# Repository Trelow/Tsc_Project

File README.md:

# OpenBook Reader

```mermaid
graph TD
    
    USB["USB-C Connector(ESD Protection)"] -->|5V| CHG["Battery Charger (MCP73831)"]
    CHG -->|Charging| BATT["Li-Po Battery (2500mAh)"]
    BATT --> LDO["3.3V LDO Regulator (XC6220)"]

    LDO -->|3.3V| ESP["ESP32-C6-WROOM-1(MCU)"]

    ESP -- I2C --> RTC["Real Time Clock(DS3231)"]
    ESP -- I2C --> BME["Environmental Sensor(BME688)"]
    ESP -- I2C --> FUEL["Battery Fuel Gauge(MAX17048)"]
    ESP -- I2C --> QWIIC["Qwiic / Stemma QT"]

    ESP -- SPI --> FLASH["External NOR Flash(W25Q512)"]
    ESP -- SPI --> SD["MicroSD Card Slot"]
    ESP -- SPI --> EPD_HEADER["E-Paper Display Header"]

    EPD_HEADER --> EPD_DRIVER["EPD Driver Circuit"]
    EPD_DRIVER --> EPD_POW["EPD HV Power"]
    LDO --> EPD_HEADER

    ESP -- GPIO --> BUTTONS["3x Buttons:BOOT, CHANGE, RESET"]

    USB -- USB D+/D- --> ESP
```

## Tabel Componente Principale (BOM)

| Parts | Device | Check Prices | Datasheet |
|-------|--------|--------------|-----------|
|R1, R2 .. | ESP32_WROVER_EAGLE-LTSPICE_RR0402 |https://componentsearchengine.com/part-view/R0402%201%25%20100%20K%20                   | https://componentsearchengine.com/part-view/R0402%201%25%20100%20K%20      |
| L1 | 744043680IND_4828-WE-TPC_WRE |  https://eu.mouser.com/ProductDetail/Wurth-Elektronik/744043680?qs=PGXP4M47uW6VkZq%252BkzjrHA%3D%3D               | https://eu.mouser.com/ProductDetail/Wurth-Elektronik/744043680?qs=PGXP4M47uW6VkZq%252BkzjrHA%3D%3D               |
| IC1 | BD5229G-TR |https://componentsearchengine.com/part-view/BD5229G-TR/ROHM%20Semiconductor                                    | https://componentsearchengine.com/part-view/BD5229G-TR/ROHM%20Semiconductor                                    |
| SENSOR2 | ESP32_WROVER_BME680_BME680 | https://www.snapeda.com/parts/BME680/Bosch/view-part/?welcome=home                                            | https://www.snapeda.com/parts/BME680/Bosch/view-part/?welcome=home                                            |
| SJ1              | SJ                                           | https://grabcad.com/library/solder-jumpers-1                                                                   | https://grabcad.com/library/solder-jumpers-1                                                                   |
| BOOT_BUTTON, CHANGE_BUTTON, RESET_BUTTON | BUTTON_CUSYOMV1 | https://industry.panasonic.com/global/en/products/control/switch/light-touch/number/evqpuj02k                  | https://industry.panasonic.com/global/en/products/control/switch/light-touch/number/evqpuj02k                  |
| C1, C2 .. | CPH3225A | https://www.snapeda.com/parts/CPH3225A/Seiko+Instruments/view-part/?ref=eda | - |
| U3 | DS3231SN# | https://www.snapeda.com/parts/DS3231SN%23/Analog+Devices/view-part/?ref=eda | [Datasheet](https://www.analog.com/media/en/technical-documentation/data-sheets/ds3231.pdf) |
| U2 | ESP32-C6-WROOM-1-N8 | https://www.snapeda.com/parts/ESP32-C6-WROOM-1-N8/Espressif+Systems/view-part/?ref=eda | - |
| PFMF.050.1 | ESP32C6_VARISTORCN1812| https://www.mouser.co.uk/ProductDetail/EPCOS-TDK/B72520T0350K062?qs=dEfas%2FXlABIszF52uu7vrg%3D%3D              | https://www.mouser.co.uk/ProductDetail/EPCOS-TDK/B72520T0350K062?qs=dEfas%2FXlABIszF52uu7vrg%3D%3D              |
| D2 | ESP32_WROVER_AVX---SD0805S020S1R0 | https://eu.mouser.com/ProductDetail/KYOCERA-AVX/SD0805S020S1R0?qs=jCA%252BPfw4LHbpkAoSnwrdjw%3D%3D              | http://datasheets.avx.com/schottky.pdf                                                                         |
| MCP73831 | ESP32_WROVER_SPARKFUN-IC-POWER_MCP73831 |  https://eu.mouser.com/ProductDetail/Microchip-Technology/MCP73831T-2ACI-OT?qs=yUQqVecv4qvbBQBGbHx0Mw%3D%3Dcf   |
| J1 | FH34SRJ-24S-0.5SH_99_ | https://componentsearchengine.com/part-view/XC6220A331MR-G/Torex                                              | https://componentsearchengine.com/part-view/XC6220A331MR-G/Torex                                              |
| U4 | MAX17048G+T10 | https://www.snapeda.com/parts/MAX17048G+T10/Analog+Devices/view-part/?ref=eda | - |
| D3, D4, D5 | MBR0530 | https://www.snapeda.com/parts/MBR0530/Onsemi/view-part/?ref=eda | - |
| D6, D8, D9, D10, D11, D12 | PGB1010603MR | https://www.snapeda.com/parts/PGB1010603MR/Littelfuse/view-part/?ref=eda | - |
| J3 | QWIIC_CONNECTORJS-1MM | - | - |
| J2 | SAMACSYS_PARTS_USB4110-GF-A |https://www.mouser.com/ProductDetail/GCT/USB4110-GF-A | https://gct.co/files/drawings/usb4110.pdf |
| D7 | ESP32_WROVER_AVX---SD0805S020S1R0 | - | [Datasheet](http://datasheets.avx.com/schottky.pdf) |
| BOOT_BUTTON | EVQPUJ02K | https://www.mouser.com/ProductDetail/Panasonic/EVQPUJ02K | [Datasheet](https://na.industrial.panasonic.com/file-download/21900) |
| Q3 | SI1308EDL-T1-GE3 | https://componentsearchengine.com/part-view/SI1308EDL-T1-GE3/Vishay                                           | https://componentsearchengine.com/part-view/SI1308EDL-T1-GE3/Vishay                                           |
| TP1, TP2, ..., TP17 | TPTP20R | - | - |
| D1 | USBLC6-2SC6Y |  https://www.snapeda.com/parts/USBLC6-2SC6Y/STMicroelectronics/view-part/?ref=eda                              | https://www.snapeda.com/parts/USBLC6-2SC6Y/STMicroelectronics/view-part/?ref=eda                              |
| U1 | W25Q512JVEIQ | https://www.snapeda.com/parts/W25Q512JVEIQ/Winbond+Electronics/view-part/?ref=eda | - |
| IC4 | XC6220A331MR-G | https://www.mouser.com/ProductDetail/Torex-Semiconductor/XC6220A331MR-G) | https://www.torexsemi.com/file/xc6220/XC6220.pdf |

## Descriere Detaliată a Funcționalității Hardware

### 1. Microcontroller – ESP32-C6
Dispozitivul folosește microcontroller-ul ESP32-C6-WROOM-1-N8, echipat cu un nucleu RISC-V pe 32 de biți, cu o frecvență maximă de 160 MHz.

- **Memorie:** 512 KB SRAM internă și flash extern de 8 MB (W25Q512JVEIQ).
- **Conectivitate:** Wi-Fi 6, Bluetooth 5 LE, interfață USB 2.0.
- **Periferice:** Suport SPI, I²C, UART și GPIO multipli.
- **Eficiență energetică:** Moduri sleep și deep sleep optimizate pentru utilizarea eficientă a bateriei.

### 2. Afișaj E-Paper
Afișaj E-Ink de 7.5” cu rezoluție de 800×480 pixeli

- **Interfață:** SPI 4-wire cu pini adiționali (CS, DC, RST, BUSY).
- **Consum:** Foarte redus în stare statică; crește doar temporar în timpul actualizării imaginii (aproximativ 15-25 mA).
- **Beneficii:** Imaginea este păstrată fără consum electric, ideal pentru dispozitive portabile tip e-reader.

### 3. Senzor Mediu – BME680
Senzor multifuncțional care măsoară temperatura, umiditatea, presiunea atmosferică și calitatea aerului (VOC/eCO₂).

- **Interfață:** I²C cu viteză de până la 400 kHz.
- **Consum:** Aproximativ 2.1µA în mod standby și câțiva mA la citiri active.
- **Avantaj principal:** Integrează multiple funcții de mediu într-un singur cip compact și eficient.

### 4. Management Energetic & Baterie
Sistemul energetic este bazat pe o baterie Li-Po de 3.7V și capacitate de 2500mAh, pentru autonomie extinsă.

- **Încărcare:** MCP73831, încărcare rapidă prin USB-C (maxim 1A).
- **Monitorizare:** MAX17048 comunică starea bateriei prin interfața I²C.
- **Regulator:** XC6220A331MR-G oferă tensiunea stabilă de 3.3V pentru componentele critice.

### 5. Interfață Utilizator – Butoane
Sunt incluse trei butoane tactile dedicate navigării, selecției și întoarcerii paginilor, fiecare conectat la GPIO cu debouncing hardware (rezistor și condensator) sau software.

### 6. Conector USB-C
- **Funcții principale:** Încărcarea acumulatorului, transferul de date (USB 2.0) și actualizarea firmware-ului. Utilizare de diode ESD (ex: USBLC6-2SC6Y) și rezistențe specifice pentru conformitate cu USB-C.

### 8. Slot MicroSD (112A-TAAR-R03)
- **Utilizare:** Stocare log-uri, cărți electronice și actualizări de firmware.
- **Interfață:** Compatibil cu SD (mod 1-bit sau 4-bit) sau SPI, configurabil în firmware.

### 8. Conector Qwiic (I²C)
Conector standardizat cu patru pini (VCC, GND, SDA, SCL) pentru extinderea rapidă a funcționalităților prin senzori sau module suplimentare.

### 9. RTC DS3231
- **Precizie:** Foarte ridicată.
- **Interfață:** Comunicare I²C integrată cu ceilalți senzori.

### 10. Memorie Flash Externă – W25Q512JVEIQ
- **Interfață:** Quad SPI pentru acces rapid la date.
- **Utilizare:** Stocarea aplicațiilor, imaginilor și fișierelor mari, inclusiv cărți electronice.

## Estimare Consum Energetic
- **Activ (Wi-Fi + refresh ecran):** Aproximativ 150 mA
- **Citire (ecran static):** Aproximativ 10 mA
- **Deep Sleep:** Sub 50 µA
- **Autonomie:** Aproximativ o săptămână, considerând un consum mediu de 10 mA (2500mAh ~250 ore utilizare).

## Estimare Consum de Energie
- **Activ (Wi-Fi + Refresh ecran)**: ~150mA  
- **Citire (ecran static)**: ~10mA  
- **Deep Sleep**: <50µA  
- **Autonomie estimată**: ~1 săptămână (la o utilizare medie de 10mA, o baterie de 2500mAh durează ~250 ore).

---

## Atribuirea Pinilor pe ESP32-C6

| Pin  | Funcție        | Componentă          | Descriere Utilizare           |
|-----:|:---------------|:--------------------|:------------------------------|
| GPIO0  | BOOT_BUTTON    | Buton               | Boot mode la pornire          |
| GPIO1  | RESET_BUTTON   | Buton               | Reset manual                  |
| GPIO2  | CHANGE_BUTTON  | Buton               | Navigare meniu                |
| GPIO3  | EPD_CS         | Display E-Paper     | Chip Select (SPI)             |
| GPIO4  | EPD_DC         | Display E-Paper     | Data/Command control          |
| GPIO5  | EPD_RST        | Display E-Paper     | Reset ecran                   |
| GPIO6  | EPD_BUSY       | Display E-Paper     | Semnal stare refresh          |
| GPIO7  | SPI_MOSI       | Display, Flash, SD  | Master Out Slave In (SPI)     |
| GPIO8  | SPI_MISO       | Display, Flash, SD  | Master In Slave Out (SPI)     |
| GPIO9  | SPI_SCK        | Display, Flash, SD  | Clock SPI                     |
| GPIO10 | FLASH_CS       | W25Q512JVEIQ        | Chip Select pentru Flash      |
| GPIO11 | SD_CS          | Micro SD (opțional) | Chip Select card SD           |
| GPIO12 | I2C_SDA        | BME680, MAX17048, DS3231 | Linie date I2C          |
| GPIO13 | I2C_SCL        | BME680, MAX17048, DS3231 | Linie clock I2C         |
| GPIO14 | CHG_LED        | LED încărcare       | Status încărcare              |
| GPIO15 | UART_TX        | Debugging           | TX serial                     |
| GPIO16 | UART_RX        | Debugging           | RX serial                     |
| GPIO17 | USB_D+         | USB-C               | Linie date USB +              |
| GPIO18 | USB_D-         | USB-C               | Linie date USB –              |

---

## Concluzii
Prin acest README, aveți la dispoziție elementele cheie ale construcției hardware pentru e-reader-ul **OpenBook**: modulul ESP32-C6, ecranul e-paper, senzorii, alimentarea și circuitele de încărcare. Fișierul CSV atașat oferă o listă detaliată a componentelor (BOM).

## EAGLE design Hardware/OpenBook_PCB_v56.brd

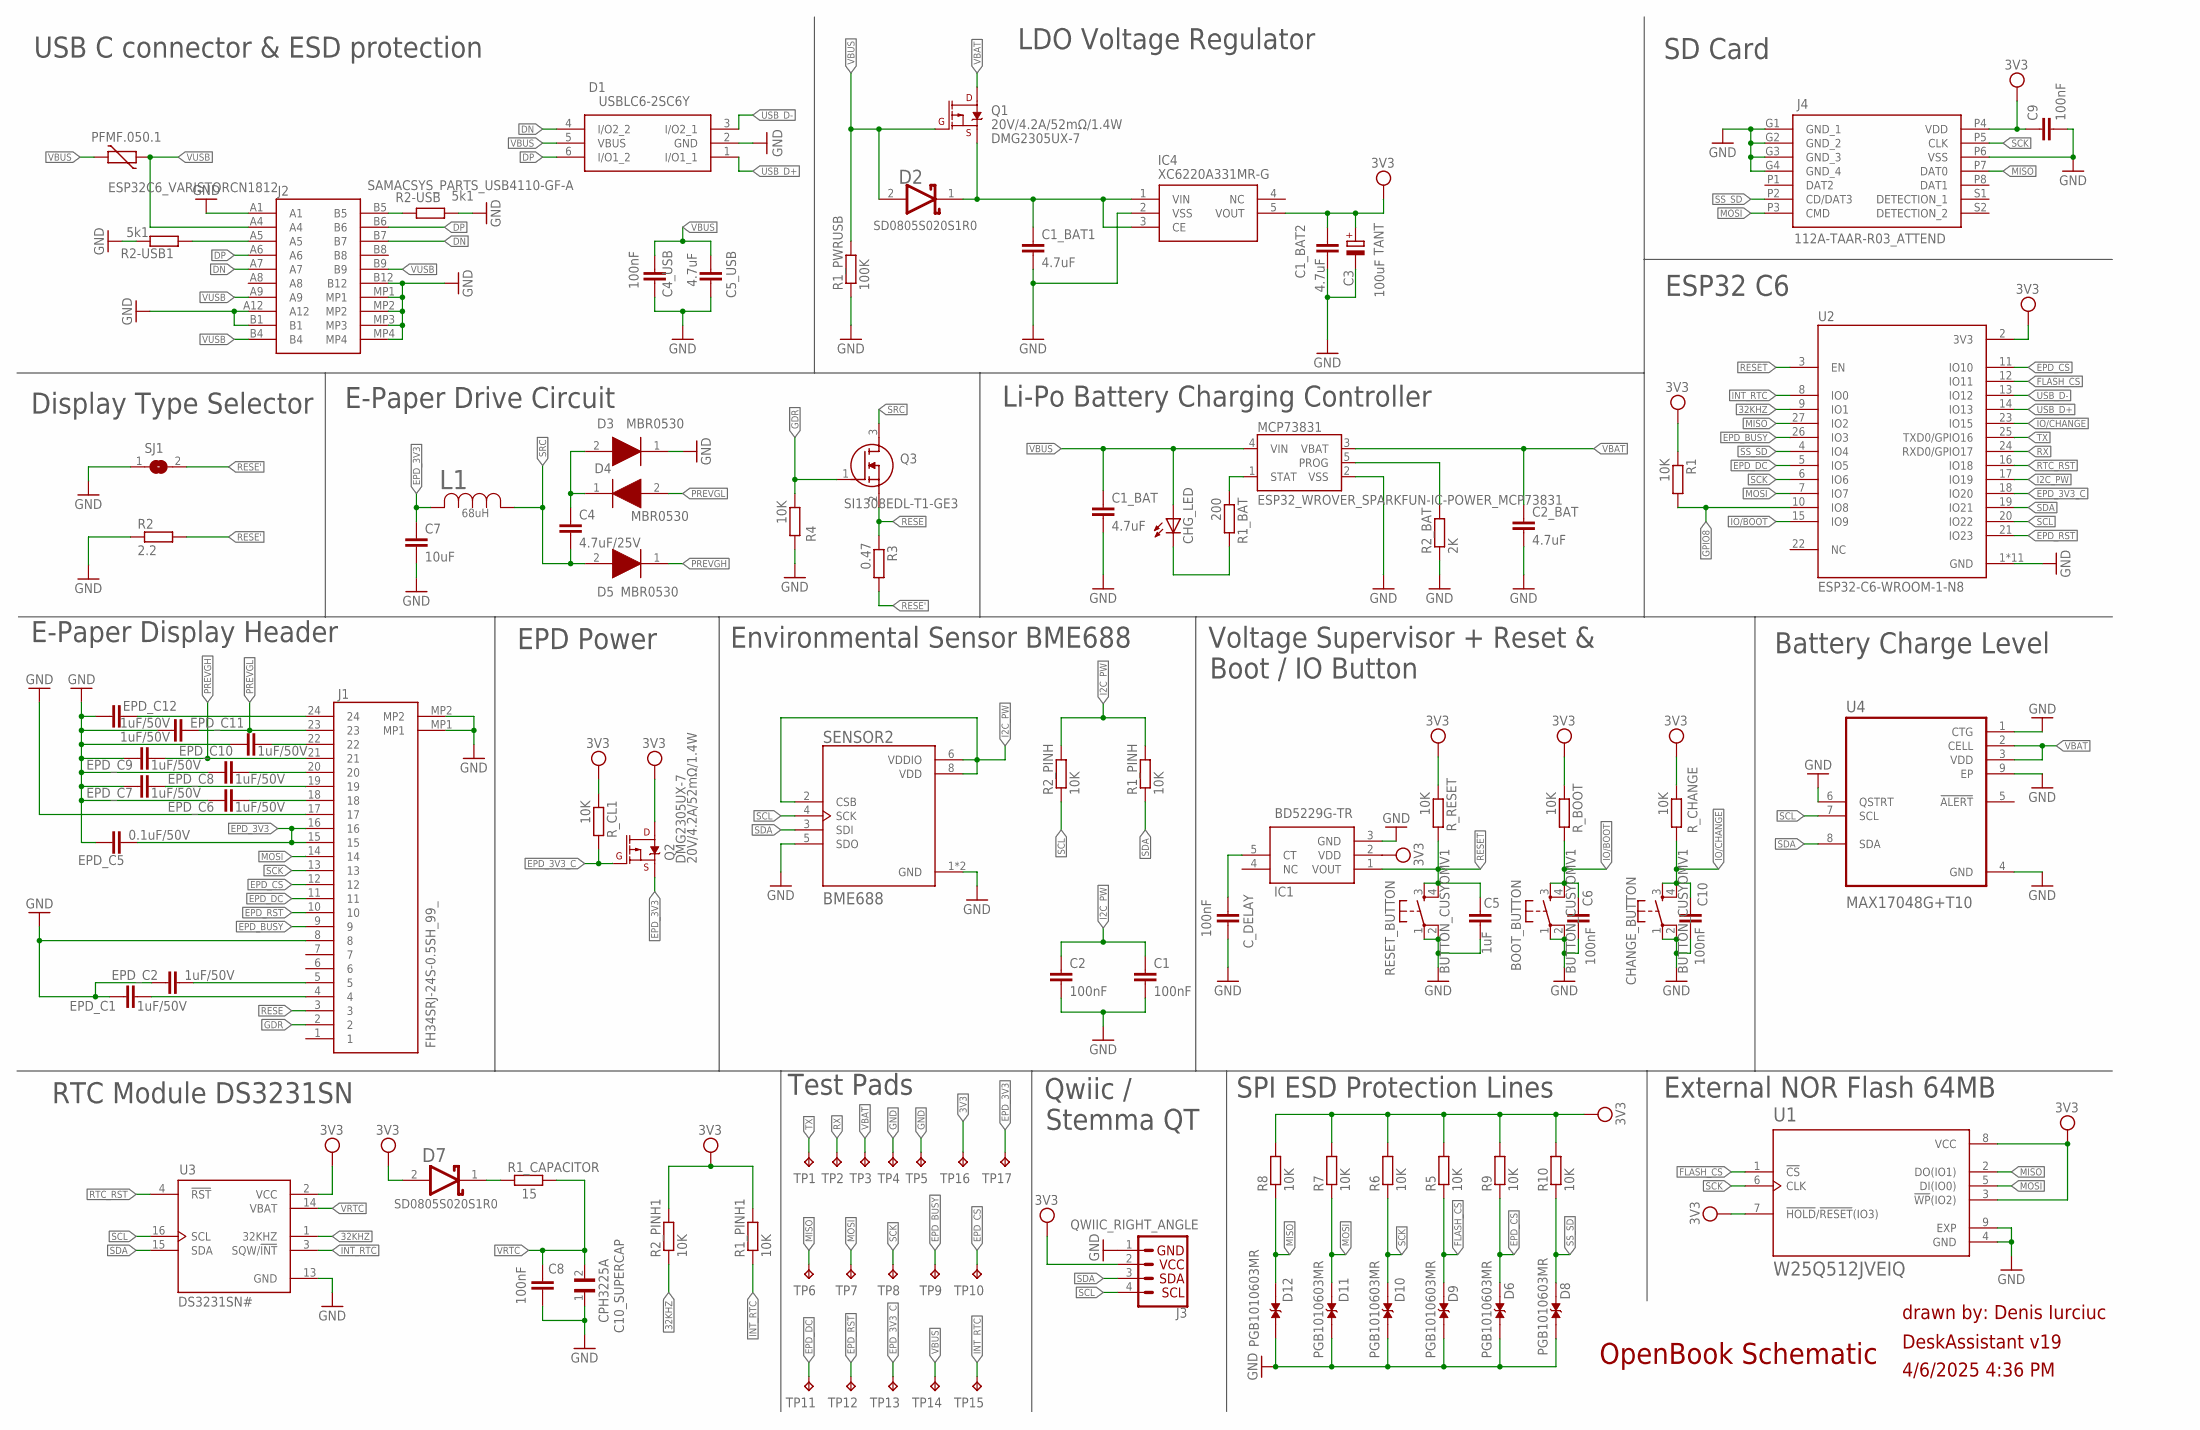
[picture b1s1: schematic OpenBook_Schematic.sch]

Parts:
BOOT_BUTTON: BUTTON_CUSYOMV1; MYBUTTON
C1, C2, C4_USB, C6, C8, C9, C10: 100nF; ESP32_WROVER_EAGLE-LTSPICE_C0402
C1_BAT, C1_BAT1, C1_BAT2, C2_BAT, C5_USB: 4.7uF; ESP32_WROVER_EAGLE-LTSPICE_C0402
C3: 100uF; RCL_CT3528
C4: 4.7uF/25V; ESP32_WROVER_EAGLE-LTSPICE_C0402
C5: 1uF; ESP32_WROVER_EAGLE-LTSPICE_C0402
C7: 10uF; ESP32_WROVER_EAGLE-LTSPICE_C0402
C10_SUPERCAP: CPH3225A; CAPCP3225X100N
CHANGE_BUTTON: BUTTON_CUSYOMV1; MYBUTTON
CHG_LED: ADAFRUIT_LEDCHIP-LED0603; ADAFRUIT_CHIP-LED0603
C_DELAY: 100nF; ESP32_WROVER_EAGLE-LTSPICE_C0402
D1: USBLC6-2SC6Y; SOT95P280X145-6N
D2: ESP32_WROVER_AVX---SD0805S020S1R0_AVX_SD0805S020S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; ESP32_WROVER_AVX---SD0805S020S1R0_AVX_SD0805S020S1R0_0
D3, D4, D5: MBR0530; SOD3716X135N
D6, D8, D9, D10, D11, D12: PGB1010603MR; DIOC1608X36N
D7: SD0805S020S1R0; ESP32_WROVER_AVX---SD0805S020S1R0_AVX_SD0805S020S1R0_0
EPD_C1, EPD_C2, EPD_C6, EPD_C7, EPD_C8, EPD_C9, EPD_C10, EPD_C11, EPD_C12: 1uF/50V; ESP32_WROVER_EAGLE-LTSPICE_C0402
EPD_C5: 0.1uF/50V; ESP32_WROVER_EAGLE-LTSPICE_C0402
IC1: BD5229G-TR; SOT95P280X125-5N
IC4: XC6220A331MR-G; SOT95P280X120-5N
J1: FH34SRJ-24S-0.5SH_99_; FH34SRJ24S05SH99
J2: SAMACSYS_PARTS_USB4110-GF-A; SAMACSYS_PARTS_USB4110GFA
J3: QWIIC_RIGHT_ANGLE; JST04_1MM_RA
J4: 112A-TAAR-R03_ATTEND; 112ATAARR03ATTEND
L1: 68uH; IND_4828-WE-TPC_WRE
MCP73831: ESP32_WROVER_SPARKFUN-IC-POWER_MCP73831; ESP32_WROVER_SPARKFUN-IC-POWER_SOT23-5
PFMF.050.1: ESP32C6_VARISTORCN1812; ESP32C6_VARISTOR_CT/CN1812
Q1, Q2: 20V/4.2A/52mΩ/1.4W; ESP32_WROVER_SPARKFUN-DISCRETESEMI_SOT23-3
Q3: SI1308EDL-T1-GE3; SOT65P210X110-3N
R1, R1_PINH, R1_PINH1, R2_PINH, R2_PINH1, R4, R5, R6, R7, R8, R9, R10: 10K; ESP32_WROVER_EAGLE-LTSPICE_R0402
R1_BAT: 200; ESP32_WROVER_EAGLE-LTSPICE_R0402
R1_CAPACITOR: 15; ESP32_WROVER_EAGLE-LTSPICE_R0402
R1_PWRUSB: 100K; ESP32_WROVER_EAGLE-LTSPICE_R0402
R2: 2.2; ESP32_WROVER_EAGLE-LTSPICE_R0402
R2-USB, R2-USB1: 5k1; ESP32_WROVER_EAGLE-LTSPICE_R0402
R2_BAT: 2K; ESP32_WROVER_EAGLE-LTSPICE_R0402
R3: 0.47; ESP32_WROVER_EAGLE-LTSPICE_R0402
RESET_BUTTON: BUTTON_CUSYOMV1; MYBUTTON
R_BOOT: 10K; ESP32_WROVER_EAGLE-LTSPICE_R0402
R_CHANGE: 10K; ESP32_WROVER_EAGLE-LTSPICE_R0402
R_CL1: 10K; ESP32_WROVER_EAGLE-LTSPICE_R0402
R_RESET: 10K; ESP32_WROVER_EAGLE-LTSPICE_R0402
SENSOR2: BME688; ESP32_WROVER_BME680_PSON80P300X300X100-8N
SJ1: SJ
TP1, TP2, TP3, TP4, TP5, TP6, TP7, TP8, TP9, TP10, TP11, TP12, TP13, TP14, TP15, TP16, TP17: TPTP20R; TP20R
U1: W25Q512JVEIQ; SON127P600X800X80-9N
U2: ESP32-C6-WROOM-1-N8; XCVR_ESP32-C6-WROOM-1-N8
U3: DS3231SN#; SOIC127P1032X265-16N
U4: MAX17048G+T10; SON50P200X200X80-9N

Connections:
3V3: C1_BAT2.1, C3.+, C9.1, D7.2 (ANODE), IC1.2 (VDD), IC4.5 (VOUT), J3.2, J4.P4 (VDD), Q2.3 (D), R1.1, R1_PINH1.2, R2_PINH1.2, R5.2, R6.2, R7.2, R8.2, R9.2, R10.2, R_BOOT.1, R_CHANGE.1, R_CL1.1, R_RESET.1, TP16.TP, U1.3 (!WP!(IO2)), U1.7 (!HOLD!/!RESET!(IO3)), U1.8 (VCC), U2.2 (3V3), U3.2 (VCC)
32KHZ: R2_PINH1.1, U2.9 (IO1), U3.1 (32KHZ)
DN: D1.4 (I/O2_2), J2.A7, J2.B7
DP: D1.6 (I/O1_2), J2.A6, J2.B6
EPD_3V3: C7.1, EPD_C5.1, J1.15, J1.16, L1.2, Q2.2 (S), TP17.TP
EPD_3V3_C: Q2.1 (G), R_CL1.2, TP13.TP, U2.18 (IO20)
EPD_BUSY: J1.9, TP9.TP, U2.26 (IO3)
EPD_CS: D6.2, J1.12, R9.1, TP10.TP, U2.11 (IO10)
EPD_DC: J1.11, TP11.TP, U2.5 (IO5)
EPD_RST: J1.10, TP12.TP, U2.21 (IO23)
FLASH_CS: D9.2, R5.1, U1.1 (!CS), U2.12 (IO11)
GDR: J1.2, Q3.1 (G), R4.1
GND: BOOT_BUTTON.1, BOOT_BUTTON.2, C1.2, C1_BAT.2, C1_BAT1.2, C1_BAT2.2, C2.2, C2_BAT.2, C3.-, C4_USB.2, C5.2, C5_USB.2, C6.2, C7.2, C8.2, C9.2, C10.2, C10_SUPERCAP.1, CHANGE_BUTTON.1, CHANGE_BUTTON.2, C_DELAY.2, D1.2 (GND), D3.1 (K), D6.1, D8.1, D9.1, D10.1, D11.1, D12.1, EPD_C1.2, EPD_C2.2, EPD_C5.2, EPD_C6.2, EPD_C7.2, EPD_C8.2, EPD_C9.2, EPD_C10.2, EPD_C11.2, EPD_C12.2, IC1.3 (GND), IC4.2 (VSS), J1.8, J1.17, J1.MP1, J1.MP2, J2.A1, J2.A12, J2.B1, J2.B12, J2.MP1, J2.MP2, J2.MP3, J2.MP4, J3.1, J4.G1 (GND_1), J4.G2 (GND_2), J4.G3 (GND_3), J4.G4 (GND_4), J4.P6 (VSS), MCP73831.2 (VSS), R1_PWRUSB.1, R2.1, R2-USB.2, R2-USB1.1, R2_BAT.1, R4.2, RESET_BUTTON.1, RESET_BUTTON.2, SENSOR2.1 (GND), SENSOR2.5 (SDO), SENSOR2.7 (GND), SJ1.1, TP4.TP, TP5.TP, U1.4 (GND), U1.9 (EXP), U2.1 (GND), U2.28 (GND), U2.29_1 (GND), U2.29_2 (GND), U2.29_3 (GND), U2.29_4 (GND), U2.29_5 (GND), U2.29_6 (GND), U2.29_7 (GND), U2.29_8 (GND), U2.29_9 (GND), U3.13 (GND), U4.1 (CTG), U4.4 (GND), U4.6 (QSTRT), U4.9 (EP)
GPIO8: R1.2, U2.10 (IO8)
I2C_PW: C1.1, C2.1, R1_PINH.2, R2_PINH.2, SENSOR2.2 (CSB), SENSOR2.6 (VDDIO), SENSOR2.8 (VDD), U2.17 (IO19)
INT_RTC: R1_PINH1.1, TP15.TP, U2.8 (IO0), U3.3 (SQW/!INT)
IO/BOOT: BOOT_BUTTON.3, BOOT_BUTTON.4, C6.1, R_BOOT.2, U2.15 (IO9)
IO/CHANGE: C10.1, CHANGE_BUTTON.3, CHANGE_BUTTON.4, R_CHANGE.2, U2.23 (IO15)
MISO: D12.2, J4.P7 (DAT0), R8.1, TP6.TP, U1.2 (DO(IO1)), U2.27 (IO2)
MOSI: D11.2, J1.14, J4.P3 (CMD), R7.1, TP7.TP, U1.5 (DI(IO0)), U2.7 (IO7)
unnamed: J2.A5, R2-USB1.2
unnamed: J2.B5, R2-USB.1
unnamed: C1_BAT1.1, D2.1 (CATHODE), IC4.1 (VIN), IC4.3 (CE), Q1.2 (S)
unnamed: EPD_C12.1, J1.24
unnamed: CHG_LED.C, R1_BAT.2
unnamed: MCP73831.1 (STAT), R1_BAT.1
unnamed: MCP73831.5 (PROG), R2_BAT.2
unnamed: C4.1, D3.2 (A), D4.1 (K)
unnamed: EPD_C10.1, J1.22
unnamed: EPD_C8.1, J1.20
unnamed: EPD_C7.1, J1.19
unnamed: EPD_C6.1, J1.18
unnamed: C_DELAY.1, IC1.5 (CT)
unnamed: D7.1 (CATHODE), R1_CAPACITOR.1
unnamed: EPD_C2.1, J1.5
unnamed: EPD_C1.1, J1.4
PREVGH: D5.1 (K), EPD_C9.1, J1.21
PREVGL: D4.2 (A), EPD_C11.1, J1.23
RESE: J1.3, Q3.2 (S), R3.1
RESE': R2.2, R3.2, SJ1.2
RESET: C5.1, IC1.1 (VOUT), RESET_BUTTON.3, RESET_BUTTON.4, R_RESET.2, U2.3 (EN)
RTC_RST: U2.16 (IO18), U3.4 (!RST)
RX: TP2.TP, U2.24 (RXD0/GPIO17)
SCK: D10.2, J1.13, J4.P5 (CLK), R6.1, TP8.TP, U1.6 (CLK), U2.6 (IO6)
SCL: J3.4, R2_PINH.1, SENSOR2.4 (SCK), U2.20 (IO22), U3.16 (SCL), U4.7 (SCL)
SDA: J3.3, R1_PINH.1, SENSOR2.3 (SDI), U2.19 (IO21), U3.15 (SDA), U4.8 (SDA)
SRC: C4.2, D5.2 (A), L1.1, Q3.3 (D)
SS_SD: D8.2, J4.P2 (CD/DAT3), R10.1, U2.4 (IO4)
TX: TP1.TP, U2.25 (TXD0/GPIO16)
USB_D+: D1.1 (I/O1_1), U2.14 (IO13)
USB_D-: D1.3 (I/O2_1), U2.13 (IO12)
VBAT: C2_BAT.1, MCP73831.3 (VBAT), Q1.3 (D), TP3.TP, U4.2 (CELL), U4.3 (VDD)
VBUS: C1_BAT.1, C4_USB.1, C5_USB.1, CHG_LED.A, D1.5 (VBUS), D2.2 (ANODE), MCP73831.4 (VIN), PFMF.050.1.2, Q1.1 (G), R1_PWRUSB.2, TP14.TP
VRTC: C8.1, C10_SUPERCAP.2, R1_CAPACITOR.2, U3.14 (VBAT)
VUSB: J2.A4, J2.A9, J2.B4, J2.B9, PFMF.050.1.1

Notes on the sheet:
USB C connector & ESD protection
LDO Voltage Regulator
Display Type Selector
E-Paper Drive Circuit
Li-Po Battery Charging Controller
E-Paper Display Header
EPD Power
Environmental Sensor BME688
Voltage Supervisor + Reset &
Boot / IO Button
RTC Module DS3231SN
Test Pads
Qwiic /
Stemma QT
SPI ESD Protection Lines
SD Card
ESP32 C6
Battery Charge Level
External NOR Flash 64MB
OpenBook Schematic
drawn by: Denis Iurciuc
DeskAssistant v19
4/6/2025 4:36 PM

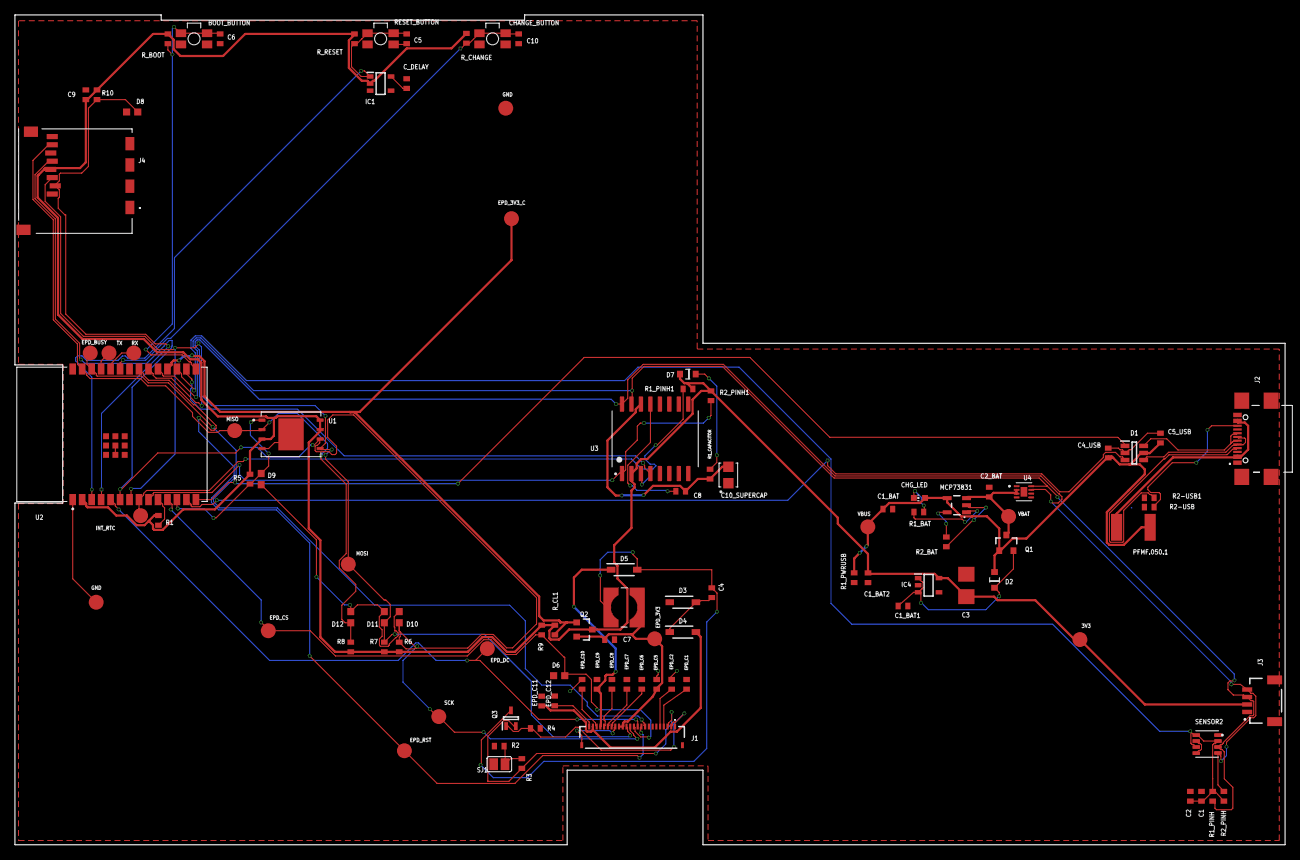
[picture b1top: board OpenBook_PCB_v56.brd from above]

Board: 2 copper layers, 170.2 x 111.2 mm, 103 parts (0 on the bottom side), 55 nets.

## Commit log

2025-04-06 final
2025-04-06 final2
2025-04-14 final3

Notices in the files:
parts and their libraries:
COPYRIGHT: Copyright (C) 2024 Ultra Librarian. All rights reserved.
